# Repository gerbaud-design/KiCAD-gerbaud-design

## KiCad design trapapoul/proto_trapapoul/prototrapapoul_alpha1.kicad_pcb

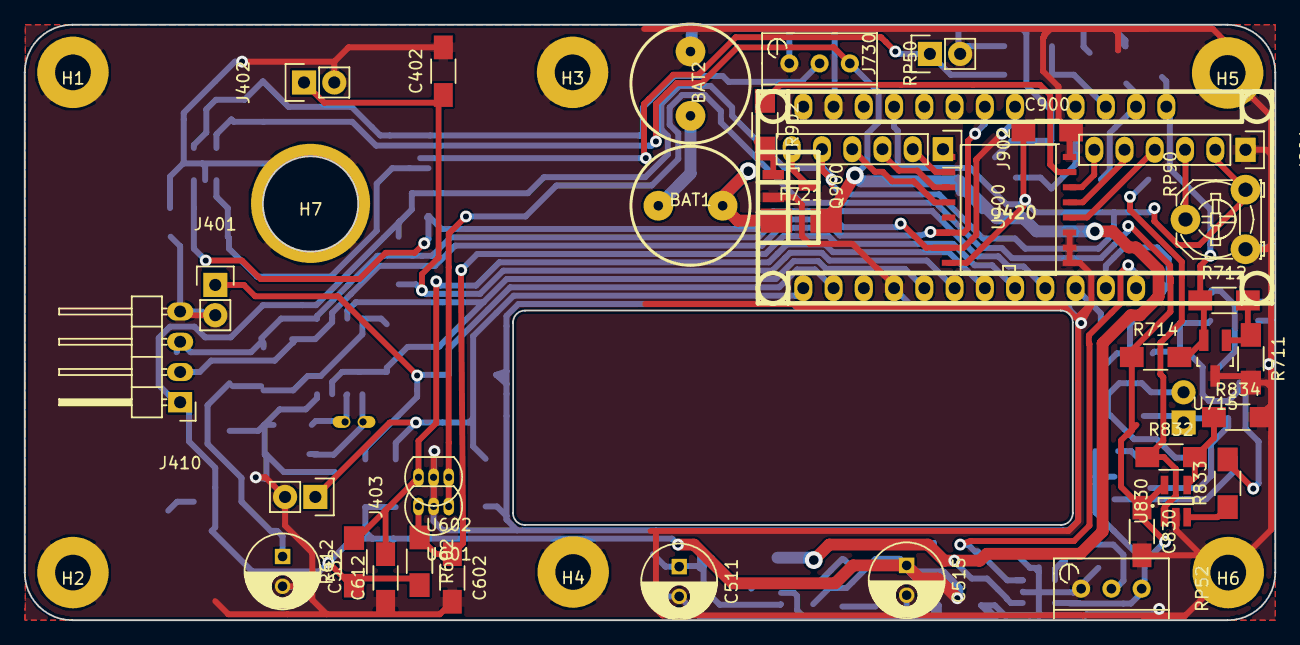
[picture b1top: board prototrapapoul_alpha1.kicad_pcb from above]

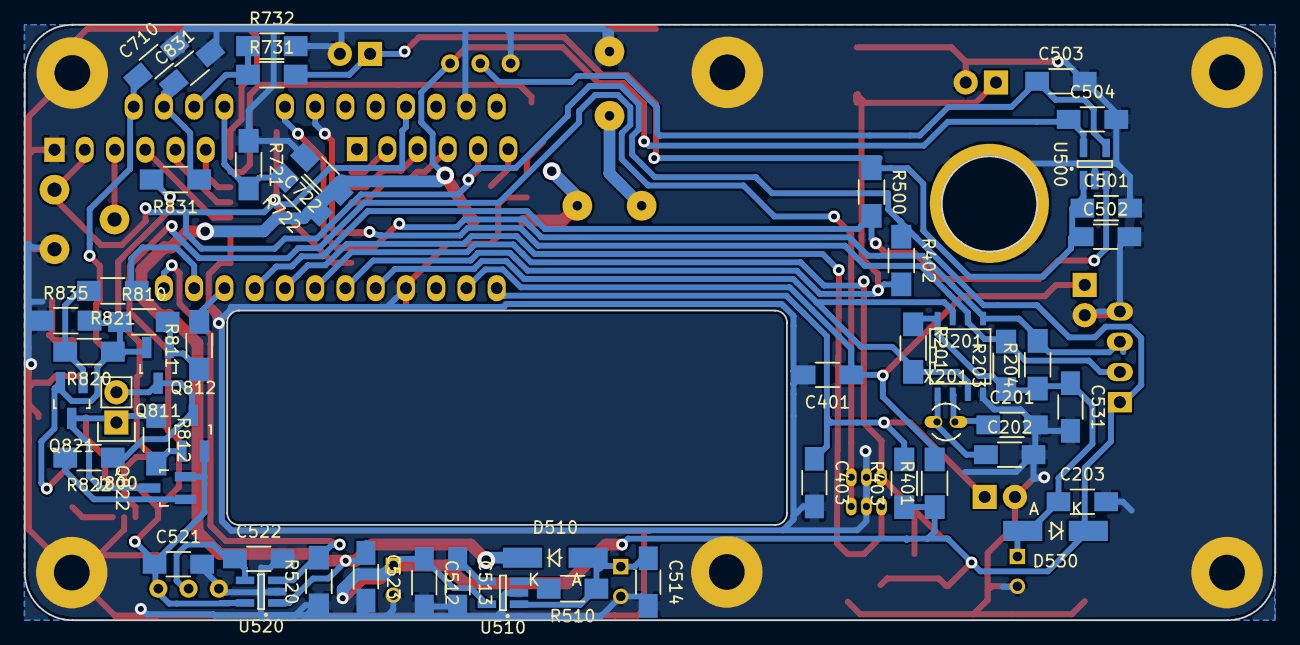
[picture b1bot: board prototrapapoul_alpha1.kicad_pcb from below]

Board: 2 copper layers, 105.0 x 50.0 mm, 96 parts (52 on the bottom side), 53 nets.

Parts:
BAT1, BAT2: BAT; HFC1025
C201, C202: 10p; C_1206_HandSoldering
C203, C401, C402, C403, C502, C503, C513, C522, C710: 10n; C_1206_HandSoldering
C501, C504, C512, C514, C521, C523, C531, C722: 10uF; C_1206_HandSoldering
C511, C515, C532: 470uF; C_Radial_D6.3_L11.2_P2.5
C602, C612, C900: 100nF; C_1206_HandSoldering
C830, C831: 100n; C_1206_HandSoldering
D510, D530: SCHOTTKY; MiniMELF_Handsoldering
F721: 5A; Fuse_SMD1206_HandSoldering
H1, H2, H3, H4, H5, H6: hole; 3mm_screw
H7: hole; MF85
J401, J402, J403, J730, J800: HEADER_2; Pin_Header_Straight_1x02
J410: HEADER_4; Pin_Header_Angled_1x04
J420: Arduino_Nano_Header; arduino_nano_header
J901, J902: HEADER_6; Pin_Header_Straight_1x06
Q811, Q821, Q900: PBSS4320; SOT-23_Handsoldering
Q812, Q822: PBSS5350; SOT-23_Handsoldering
R201, R401, R402, R403, R500, R510, R520, R711, R712, R714, R721, R722, R731, R732, R832: 10k; R_1206_HandSoldering
R203, R204: 2.2k; R_1206_HandSoldering
R602, R612: 4k7; R_1206_HandSoldering
R810, R820: 3k3; R_1206_HandSoldering
R811, R812, R821, R822: 330; R_1206_HandSoldering
R831, R833, R834: 1k; R_1206_HandSoldering
R835: 0R2; R_1206_HandSoldering
R902: 4.7k; R_1206_HandSoldering
RP50, RP52: 10k; Potentiometer_Bourns_3296W_3-8Zoll_Inline_ScrewUp
RP90: 10k; Potentiometer_Triwood_RM-065
U201: DS1337; SOIC-8-N
U500, U510, U520: MIC5205; SOT-23-5_Handsoldering
U601, U602: A3144; TO-92_Inline_Narrow_Oval
U715: TL431; SOT-23_Handsoldering
U830: MCP6001; SOT-23-5_Handsoldering
U900: PCF8574; SO-16-W
X201: 32.768K; Crystal_Round_Vertical_3mm_BigPad

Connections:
BP1: C401.1, J401.1, J420.2, R401.2
BP2: C402.1, J402.1, J420.6, R402.2
BP3: C403.1, J403.1, J420.1, R403.2
C_bkw: J420.11, R821.1
C_frw: J420.10, R811.2
GND: BAT2.2, C201.2, C202.2, C203.2, C401.2, C402.2, C403.2, C501.2, C502.2, C503.2, C504.2, C511.2, C512.2, C513.2, C514.2, C515.2, C521.2, C522.2, C523.2, C531.2, C532.2, C602.2, C612.1, C710.2, C722.2, C830.2, C831.2, C900.2, H1.1, H2.1, H3.1, H4.1, H5.1, H6.1, H7.1, J401.2, J402.2, J403.2, J410.4, J420.4, J420.29, J730.2, J901.1, Q900.2, R520.1, R711.2, R721.1, R732.2, R834.2, R835.1, RP50.1, RP52.1, RP90.1, U201.4, U500.2, U510.2, U520.2, U601.2, U602.2, U715.3, U830.2, U900.1, U900.2, U900.3, U900.8
M_bat: J420.21, R721.2, R722.2
M_imot: C831.1, J420.19, R831.1
M_sol: J420.20, R731.1, R732.1
unnamed: BAT1.1, F721.1
unnamed: BAT1.2, BAT2.1
unnamed: C201.1, U201.2, X201.2
unnamed: C202.1, U201.1, X201.1
unnamed: C503.1, RP50.2, U500.4
unnamed: C511.1, C514.1, D510.2, R510.1, U510.1
unnamed: C513.1, U510.4
unnamed: C522.1, RP52.2, U520.4
unnamed: J901.3, RP90.2
unnamed: J901.4, U900.4
unnamed: J901.5, U900.5
unnamed: J901.6, U900.6
unnamed: J902.1, U900.9
unnamed: J902.2, U900.10
unnamed: J902.3, U900.11
unnamed: J902.4, U900.12
unnamed: J902.6, Q900.3
unnamed: Q811.1, R810.2, R811.1
unnamed: Q811.2, Q821.2, R810.1, R820.1, R833.2, R835.2
unnamed: Q812.1, R812.2
unnamed: Q821.1, R820.2, R821.2
unnamed: Q822.1, R822.2
unnamed: Q900.1, R902.2
unnamed: R510.2, U510.3
unnamed: R711.1, R712.2, U715.1
unnamed: R831.2, R832.1, U830.1
unnamed: R832.2, R834.1, U830.4
unnamed: R833.1, U830.3
unnamed: R902.1, U900.7
SCL: J410.2, J420.24, R203.2, U201.6, U900.14
SDA: J410.3, J420.23, R204.2, U201.5, U900.15
VCC: C512.1, C515.1, C900.1, D530.1, J410.1, J420.27, J901.2, J902.5, R401.1, R402.1, R403.1, R602.2, R612.1, RP90.3, U510.5, U900.16
VPP: C521.1, C830.1, Q812.2, Q822.2, R714.1, RP52.3, U520.5, U601.1, U602.1, U830.5
V_bat: C504.1, C523.1, C722.1, D510.1, F721.2, R722.1, RP50.3, U500.5, U520.1
V_ref: C710.1, J420.18, R712.1, R714.2, U715.2
V_rtc: C203.1, C531.1, C532.1, D530.2, R201.1, R203.1, R204.1, U201.8
V_sol: C501.1, C502.1, J730.1, R500.1, R731.2, U500.1
VppEn: J420.12, R520.2, U520.3
alarm: J420.5, R201.2, U201.3, U201.7
charge_OFF: J420.9, R500.2, U500.3
mot_A: J800.1, Q821.3, Q822.3, R812.1
mot_B: J800.2, Q811.3, Q812.3, R822.1
quadA: C602.1, J420.8, R602.1, U601.3
quadB: C612.2, J420.7, R612.2, U602.3

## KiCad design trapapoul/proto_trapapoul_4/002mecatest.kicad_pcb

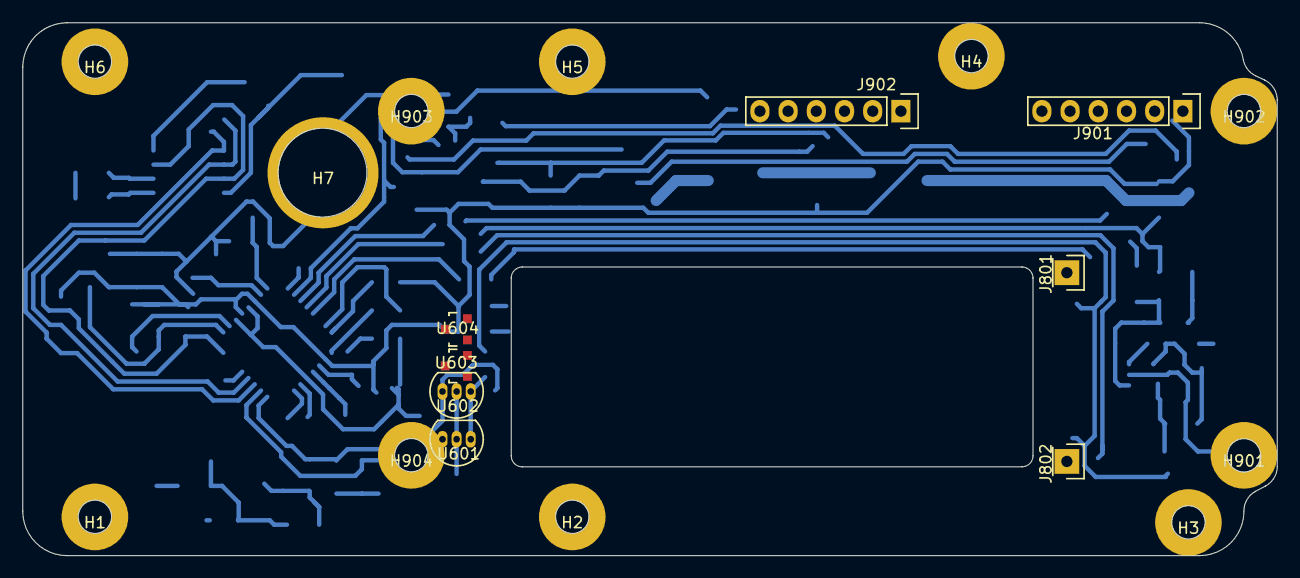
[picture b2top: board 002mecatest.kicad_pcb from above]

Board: 2 copper layers, 113.0 x 48.0 mm, 19 parts (0 on the bottom side), 5 nets.

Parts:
H1, H2, H3, H4, H5, H6, H901, H902, H903, H904: hole; 3mm_screw
H7: hole; MF85
J801, J802: HEADER_1; Pin_Header_Straight_1x01
J901, J902: HEADER_6; Pin_Header_Straight_1x06
U601, U602: A3144; TO-92_Inline_Narrow_Oval
U603, U604: A3144; SOT-23

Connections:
GND: H1.1, H2.1, H3.1, H4.1, H5.1, H6.1, H7.1, H901.1, H902.1, H903.1, H904.1, J901.1, U601.2, U602.2, U603.3, U604.3
VCC: J901.2, J902.5
VPP: U601.1, U602.1, U603.1, U604.1
quadA: U601.3, U603.2
quadB: U602.3, U604.2
